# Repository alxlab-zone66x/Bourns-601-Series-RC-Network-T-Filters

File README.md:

# Bourns 601 Series - RC Network T-Filters

This is a recreation the discontinued *Bourns 4120R-601-250/201* DIP used on the Macintosh SE and Macintosh SE/30. The filter chip also goes by the model numbers *M/C 8908L 115-0002*, *CRL 8743L 115-0002* or *P9120M115-0006*. 

Pictures of the chips:

Even though the Kicad and EasyEDA files are geared towards the *4120R-601-250/201* specifically,  the capacitor and resistor values can be changed  to make other discontinued Bourns 601 Series filters:

| Part Number       | Resistor Value | Capacitor Value |
| ----------------- | -------------- | --------------- |
| 4120R-601-101/101 | 100 ohm        | 100 pF          |
| 4120R-601-101/181 | 100 ohm        | 180 pF          |
| 4120R-601-101/201 | 100 ohm        | 200 pF          |
| 4120R-601-250/101 | 25 ohm         | 100 pF          |
| 4120R-601-250/181 | 25 ohm         | 180 pF          |
| 4120R-601-250/201 | 25 ohm         | 200 pF          |
| 4120R-601-250/500 | 25 ohm         | 50 pF           |
| 4120R-601-270/101 | 27 ohm         | 100 pF          |
| 4120R-601-270/201 | 27 ohm         | 200 pF          |
| 4120R-601-270/500 | 27 ohm         | 50 pF           |
| 4120R-601-470/101 | 47 ohm         | 100 pF          |
| 4120R-601-470/201 | 47 ohm         | 200 pF          |
| 4120R-601-470/500 | 47 ohm         | 50 pF           |
| 4120R-601-820/101 | 82 ohm         | 100 pF          |
| 4120R-601-820/201 | 82 ohm         | 200 pF          |
| 4120R-601-820/500 | 82 ohm         | 50 pF           |

If the part number your looking for isn't listed, please refer to the [datasheet](docs/datasheets/Bourns_4120R-601-250_201.pdf).

## Bill of Materials

4120R-601-250/201

| Quantity | Description                                              | Designators | Product Number  | Datasheet                                                    |
| :------- | -------------------------------------------------------- | ----------- | --------------- | ------------------------------------------------------------ |
| 16       | 25 Ohm resistor - 0402 (original 25V, ±10%)              | R1-R16      | 0402WGF255JTCE  | [datasheet](docs/datasheets/R1-R16_2110260430_UNI-ROYAL-Uniroyal-Elec-0402WGF255JTCE_C129579.pdf) |
| 8        | 200 pF capacitor - 0603 (original Z5U, ±30% capacitance) | C1-C8       | 0603CG201J500NT | [datasheet](docs/datasheets/C1-C8_1811061810_FH-Guangdong-Fenghua-Advanced-Tech-0603B201K500NT_C1600.pdf) |
| 2        | 10-pin male header 0.1" (2.54mm) pitch                   |             |                 |                                                              |

## Manufacturing

The release includes the manufacturing files for JLCPCB specifically for a 8 column and 3 row panel. The pick and place file includes all the components already placed for the panel. I recommend a PCB thickness of 1mm or less if you do panelization to make the PCBs easier to separate.

When you place an order with JLCPCB the `Delivery Format` should be `Panel by Customer` . The `Panel Format` should be `Column: 8` and `Row: 3`. The PCB Thickness should be 1mm.

The PCB preview should look like this:

For the `Bill of Materials`  part of the order where you upload the BOM and Pick and Place files there is an option at the bottom called `File provided as`. You should select `Complete File, just proceed with my own files ` since the pick and place file has all the component placements for the panel.

If you had selected everything properly you should have a minimum of 1920 resistors and 960 capacitors for a minimum order of 5 panels. JLCPCB may add a few extra resistors or capacitors to the quantities.

The assembly preview should also show all the components in the right spots. Ignore the fact that the cuts in between the individual PCBs of the panel don't show up in the component placement preview. This is normal when doing the panelization with EasyEDA.

**Note:** If you need the gerber files, BOM or component pick & place in a different format then you would have to generate them yourself.

## License

Bourns 601 Series - RC Network T-Filters by [Alexandre Marcoux](https://github.com/alxlab-zone66x/Bourns-601-Series-RC-Network-T-Filters) is licensed under a [Creative Commons Attribution 4.0 International License](http://creativecommons.org/licenses/by/4.0/).

## Community

For more great retro hardware projects and a great community check out:

Join us in #skunkworks on [Discord](https://discord.gg/GKcvtgU7P9) to help make retro solutions available to all.

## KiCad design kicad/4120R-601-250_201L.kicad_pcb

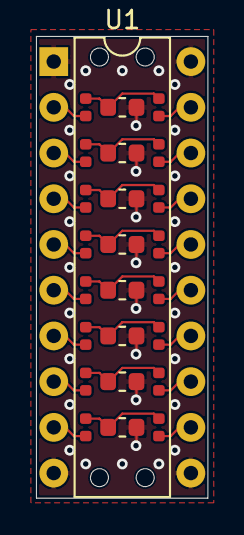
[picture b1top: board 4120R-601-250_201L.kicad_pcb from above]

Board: 2 copper layers, 9.5 x 25.7 mm, 25 parts (0 on the bottom side), 25 nets.

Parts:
C1, C2, C3, C4, C5, C6, C7, C8: 200pF; C_0603_1608Metric
R1, R2, R3, R4, R5, R6, R7, R8, R9, R10, R11, R12, R13, R14, R15, R16: 25Ω; R_0402_1005Metric
U1: Bourns_Filter_4120R-601-250_201; DIP-20_W7.62mm

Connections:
GND: C1.2, C2.2, C3.2, C4.2, C5.2, C6.2, C7.2, C8.2, U1.1, U1.10, U1.11, U1.20
unnamed: C1.1, R1.2, R2.1
unnamed: C2.1, R3.2, R4.1
unnamed: C3.1, R5.2, R6.1
unnamed: C4.1, R7.2, R8.1
unnamed: C5.1, R9.2, R10.1
unnamed: C6.1, R11.2, R12.1
unnamed: C7.1, R13.2, R14.1
unnamed: C8.1, R15.2, R16.1
unnamed: R1.1, U1.2
unnamed: R2.2, U1.19
unnamed: R3.1, U1.3
unnamed: R4.2, U1.18
unnamed: R5.1, U1.4
unnamed: R6.2, U1.17
unnamed: R7.1, U1.5
unnamed: R8.2, U1.16
unnamed: R9.1, U1.6
unnamed: R10.2, U1.15
unnamed: R11.1, U1.7
unnamed: R12.2, U1.14
unnamed: R13.1, U1.8
unnamed: R14.2, U1.13
unnamed: R15.1, U1.9
unnamed: R16.2, U1.12

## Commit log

2022-03-29 Version 1
2022-05-12 Fix BOM part numbers
2022-05-12 Change gerber archive name
2022-05-12 Change archive name again
2022-05-24 Update README to include manufacturing details and better BOM
2023-03-23 Update README with better JLCPCB manufacturing instructions
2023-03-23 Forgot to commit some changes to the README in the previous commit
2023-06-01 Update information about JLCPCB expected component quantities
